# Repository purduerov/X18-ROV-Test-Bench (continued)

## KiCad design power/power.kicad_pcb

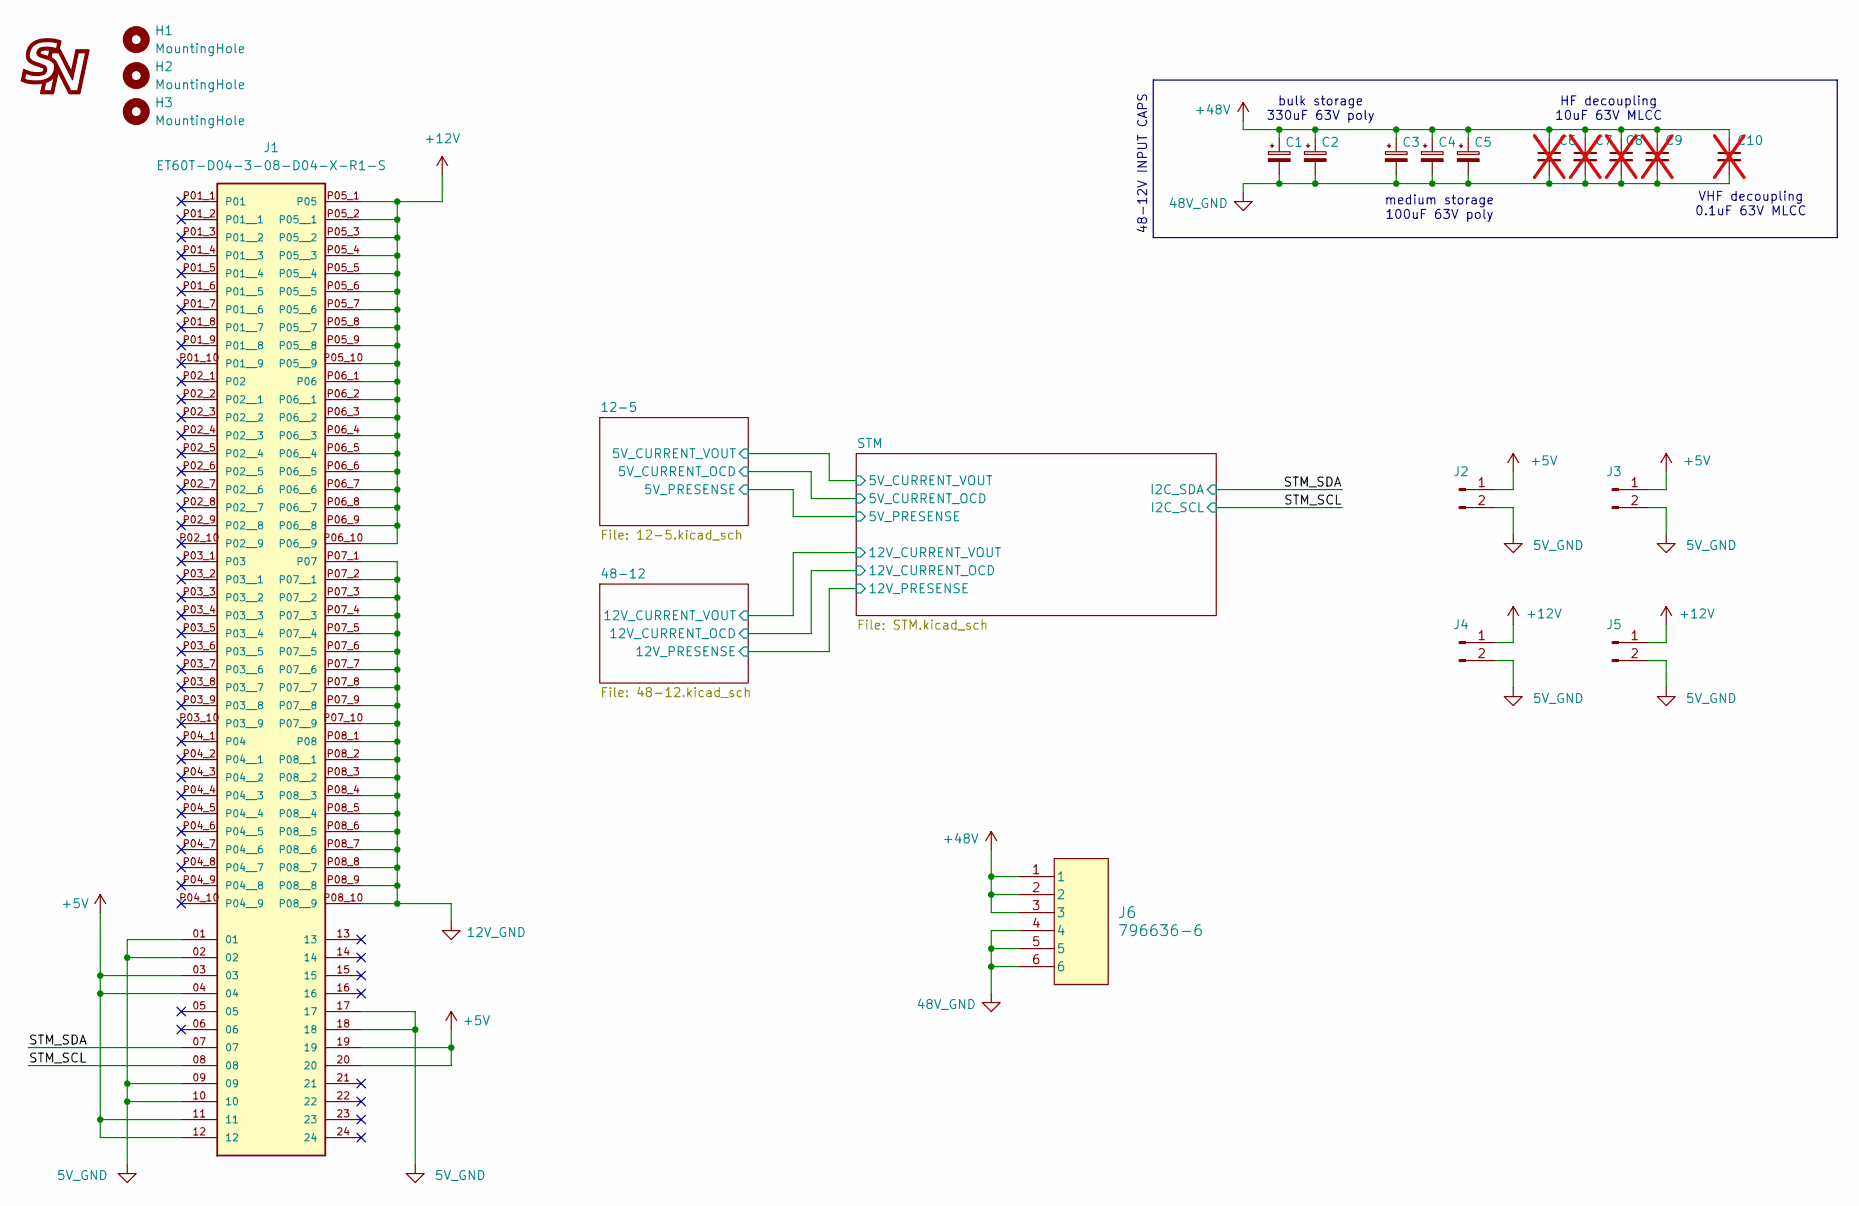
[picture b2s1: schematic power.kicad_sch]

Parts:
C1, C2: 330uF 63V poly; CP_Radial_D12.5mm_P5.00mm; MPN 63YXJ330M12.5X20; LCSC C437640
C3, C4, C5: 100uF 63V poly; CP_Radial_D8.0mm_P3.50mm; MPN RXW101M1JBK-0815; LCSC C134638
C6, C7, C8, C9: 10uF 63V; C_0603_1608Metric; not fitted
C10: 0.1uF 63V; C_0603_1608Metric; not fitted
G1: LOGO; logo
H1, H2, H3: MountingHole; MountingHole_3.2mm_M3
J1: ET60T-D04-3-08-D04-X-R1-S; SAMTEC_ET60T-D04-3-08-D04-X-R1-S
J2, J3, J4, J5: 2.54mm header; PinHeader_1x02_P2.54mm_Vertical
J6: 796636-6; MPN 796636-6

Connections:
12V_GND: J1.01, J1.02, J1.09, J1.10, J1.17, J1.18, J1.P07_1 (P07), J1.P07_2 (P07__1), J1.P07_3 (P07__2), J1.P07_4 (P07__3), J1.P07_5 (P07__4), J1.P07_6 (P07__5), J1.P07_7 (P07__6), J1.P07_8 (P07__7), J1.P07_9 (P07__8), J1.P07_10 (P07__9), J1.P08_1 (P08), J1.P08_2 (P08__1), J1.P08_3 (P08__2), J1.P08_4 (P08__3), J1.P08_5 (P08__4), J1.P08_6 (P08__5), J1.P08_7 (P08__6), J1.P08_8 (P08__7), J1.P08_9 (P08__8), J1.P08_10 (P08__9), J2.2, J3.2, J4.2, J5.2; also elsewhere on the board
48V_GND: C1.2, C2.2, C3.2, C4.2, C5.2, C6.2, C7.2, C8.2, C9.2, C10.2, J6.4, J6.5, J6.6; also elsewhere on the board
+5V: J1.03, J1.04, J1.11, J1.12, J1.19, J1.20, J2.1, J3.1; also elsewhere on the board
+12V: J1.P05_1 (P05), J1.P05_2 (P05__1), J1.P05_3 (P05__2), J1.P05_4 (P05__3), J1.P05_5 (P05__4), J1.P05_6 (P05__5), J1.P05_7 (P05__6), J1.P05_8 (P05__7), J1.P05_9 (P05__8), J1.P05_10 (P05__9), J1.P06_1 (P06), J1.P06_2 (P06__1), J1.P06_3 (P06__2), J1.P06_4 (P06__3), J1.P06_5 (P06__4), J1.P06_6 (P06__5), J1.P06_7 (P06__6), J1.P06_8 (P06__7), J1.P06_9 (P06__8), J1.P06_10 (P06__9), J4.1, J5.1; also elsewhere on the board
+48V: C1.1, C2.1, C3.1, C4.1, C5.1, C6.1, C7.1, C8.1, C9.1, C10.1, J6.1, J6.2, J6.3; also elsewhere on the board
/STM_SCL: J1.08; also elsewhere on the board
/STM_SDA: J1.07; also elsewhere on the board

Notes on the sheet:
VHF decoupling 0.1uF 63V MLCC
medium storage 100uF 63V poly
HF decoupling 10uF 63V MLCC
bulk storage 330uF 63V poly
48-12V INPUT CAPS

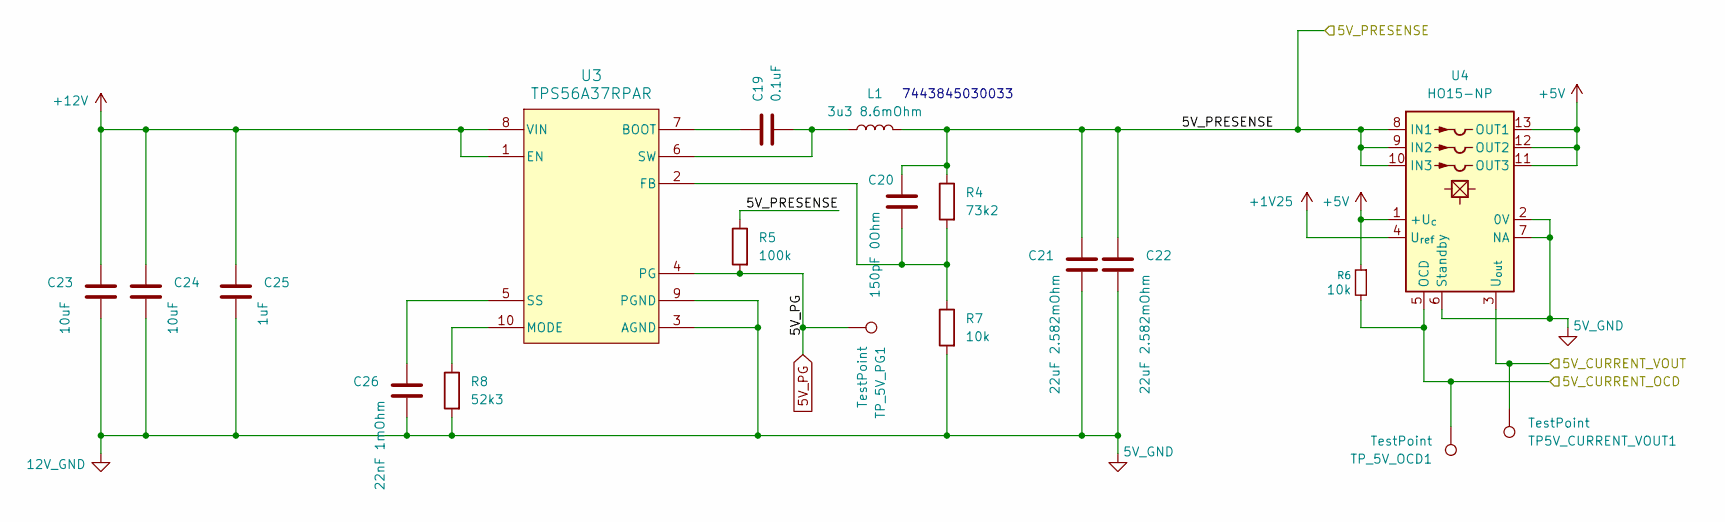
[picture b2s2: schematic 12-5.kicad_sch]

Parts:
C19: 0.1uF; C_0603_1608Metric; MPN CC0603KRX7R9BB104; LCSC C14663
C20: 150pF 0Ohm; C_0603_1608Metric; MPN CC0603JRNPO9BN151; LCSC C107038
C21, C22: 22uF 2.582mOhm; C_0603_1608Metric; MPN CL10A226MO7JZNC; LCSC C2762594
C23, C24: 10uF; C_0603_1608Metric; MPN CL10A106MA8NRNC; LCSC C96446
C25: 1uF; C_0603_1608Metric; MPN CL10A105KB8NNNC; LCSC C15849
C26: 22nF 1mOhm; C_0603_1608Metric; MPN CC0603KRX7R9BB223; LCSC C106222
L1: 3u3 8.6mOhm; WE-MXGI_5030; MPN 7443845030033
R4: 73k2; R_0603_1608Metric; MPN 0603WAF7322T5E; LCSC C14890
R5: 100k; R_0603_1608Metric; MPN 0603WAF1003T5E; LCSC C25803
R6, R7: 10k; R_0603_1608Metric; MPN 0603WAF1002T5E; LCSC C25804
R8: 52k3; R_0603_1608Metric; MPN 0603WAF5232T5E; LCSC C23198
TP5V_CURRENT_VOUT1: TestPoint; TestPoint_THTPad_2.5x2.5mm_Drill1.2mm
TP_5V_OCD1, TP_5V_PG1: TestPoint; TestPoint_THTPad_2.5x2.5mm_Drill1.2mm
U3: TPS56A37RPAR; MPN TPS56A37RPAR
U4: HO15-NP; LEM_HO8-NP; MPN HO 15-NP-0000

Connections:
5V_PG: R5.2, TP_5V_PG1.1, U3.4 (PG); also elsewhere on the board
12V_GND: C21.2, C22.2, C23.2, C24.2, C25.2, C26.2, R7.2, R8.2, U3.3 (AGND), U3.9 (PGND), U4.2 (0V), U4.6 (Standby), U4.7 (NA); also elsewhere on the board
+1V25: U4.4 (U_{ref}); also elsewhere on the board
+5V: R6.1, U4.1 (+U_{c}), U4.11 (OUT3), U4.12 (OUT2), U4.13 (OUT1); also elsewhere on the board
+12V: C23.1, C24.1, C25.1, U3.1 (EN), U3.8 (VIN); also elsewhere on the board
/12-5/5V_CURRENT_OCD: R6.2, TP_5V_OCD1.1, U4.5 (OCD); also elsewhere on the board
/12-5/5V_CURRENT_VOUT: TP5V_CURRENT_VOUT1.1, U4.3 (U_{out}); also elsewhere on the board
/12-5/5V_PRESENSE: C20.1, C21.1, C22.1, L1.2, R4.1, R5.1, U4.8 (IN1), U4.9 (IN2), U4.10 (IN3); also elsewhere on the board
unnamed: C19.1, U3.7 (BOOT)
unnamed: C20.2, R4.2, R7.1, U3.2 (FB)
unnamed: R8.1, U3.10 (MODE)
unnamed: C26.1, U3.5 (SS)
unnamed: C19.2, L1.1, U3.6 (SW)

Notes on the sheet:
7443845030033

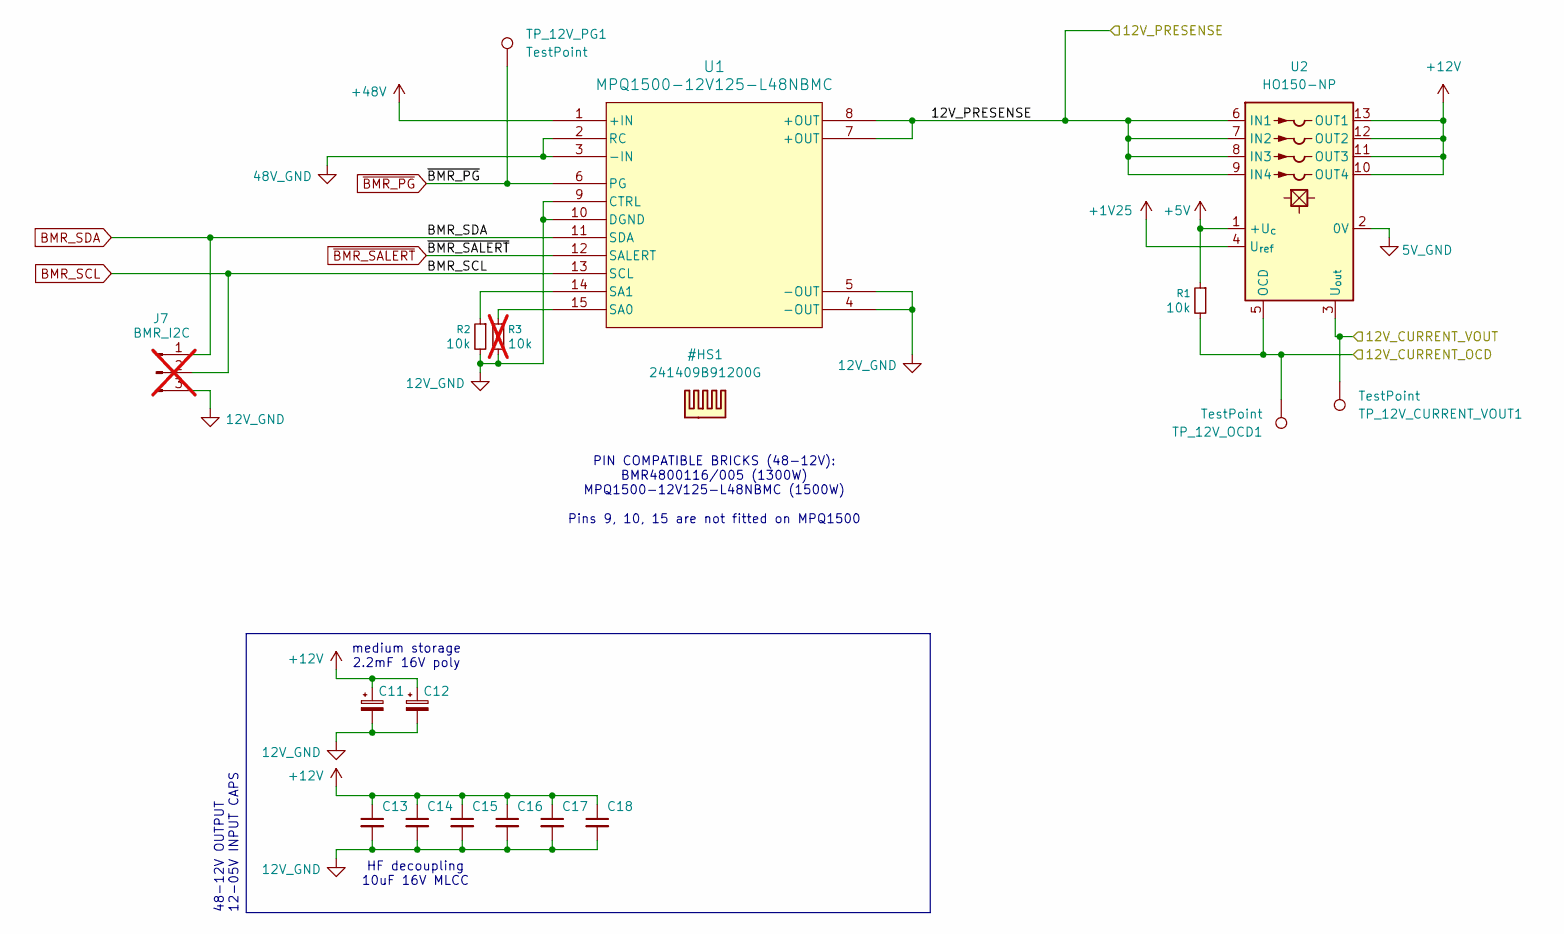
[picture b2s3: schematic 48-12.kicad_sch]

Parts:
C11, C12: 2.2mF 16V poly; CP_Radial_D18.0mm_P7.50mm; MPN GR1J222MM300A00CV0; LCSC C240374
C13, C14, C15, C16, C17, C18: 10uF; C_0603_1608Metric; MPN CL10A106MA8NRNC; LCSC C96446
J7: BMR_I2C; PinHeader_1x03_P2.54mm_Vertical; not fitted
R1, R2: 10k; R_0603_1608Metric; MPN 0603WAF1002T5E; LCSC C25804
R3: 10k; R_0603_1608Metric; MPN 0603WAF1002T5E; LCSC C25804; not fitted
TP_12V_CURRENT_VOUT1, TP_12V_OCD1, TP_12V_PG1: TestPoint; TestPoint_THTPad_2.5x2.5mm_Drill1.2mm
U1: MPQ1500-12V125-L48NBMC; BMR491_FPM; MPN MPQ1500-12V125-L48NBMC
U2: HO150-NP; LEM_HO150-NP; MPN HO 150-NP-0100

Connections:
12V_GND: C11.2, C12.2, C13.2, C14.2, C15.2, C16.2, C17.2, C18.2, J7.3, R2.2, R3.2, U1.4 (-OUT), U1.5 (-OUT), U1.9 (CTRL), U1.10 (DGND), U2.2 (0V); also elsewhere on the board
48V_GND: U1.2 (RC), U1.3 (-IN); also elsewhere on the board
+1V25: U2.4 (U_{ref}); also elsewhere on the board
+5V: R1.1, U2.1 (+U_{c}); also elsewhere on the board
+12V: C11.1, C12.1, C13.1, C14.1, C15.1, C16.1, C17.1, C18.1, U2.10 (OUT4), U2.11 (OUT3), U2.12 (OUT2), U2.13 (OUT1); also elsewhere on the board
+48V: U1.1 (+IN); also elsewhere on the board
/48-12/12V_CURRENT_OCD: R1.2, TP_12V_OCD1.1, U2.5 (OCD); also elsewhere on the board
/48-12/12V_CURRENT_VOUT: TP_12V_CURRENT_VOUT1.1, U2.3 (U_{out}); also elsewhere on the board
/48-12/12V_PRESENSE: U1.7 (+OUT), U1.8 (+OUT), U2.6 (IN1), U2.7 (IN2), U2.8 (IN3), U2.9 (IN4); also elsewhere on the board
BMR_SCL: J7.2, U1.13 (SCL); also elsewhere on the board
BMR_SDA: J7.1, U1.11 (SDA); also elsewhere on the board
unnamed: R3.1, U1.15 (SA0)
unnamed: R2.1, U1.14 (SA1)
~BMR_PG: TP_12V_PG1.1, U1.6 (PG); also elsewhere on the board
~BMR_SALERT: U1.12 (SALERT); also elsewhere on the board

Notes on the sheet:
HF decoupling 10uF 16V MLCC
PIN COMPATIBLE BRICKS (48-12V): BMR4800116/005 (1300W) MPQ1500-12V125-L48NBMC (1500W) Pins 9, 10, 15 are not fitted on MPQ1500
medium storage 2.2mF 16V poly
48-12V OUTPUT 12-05V INPUT CAPS

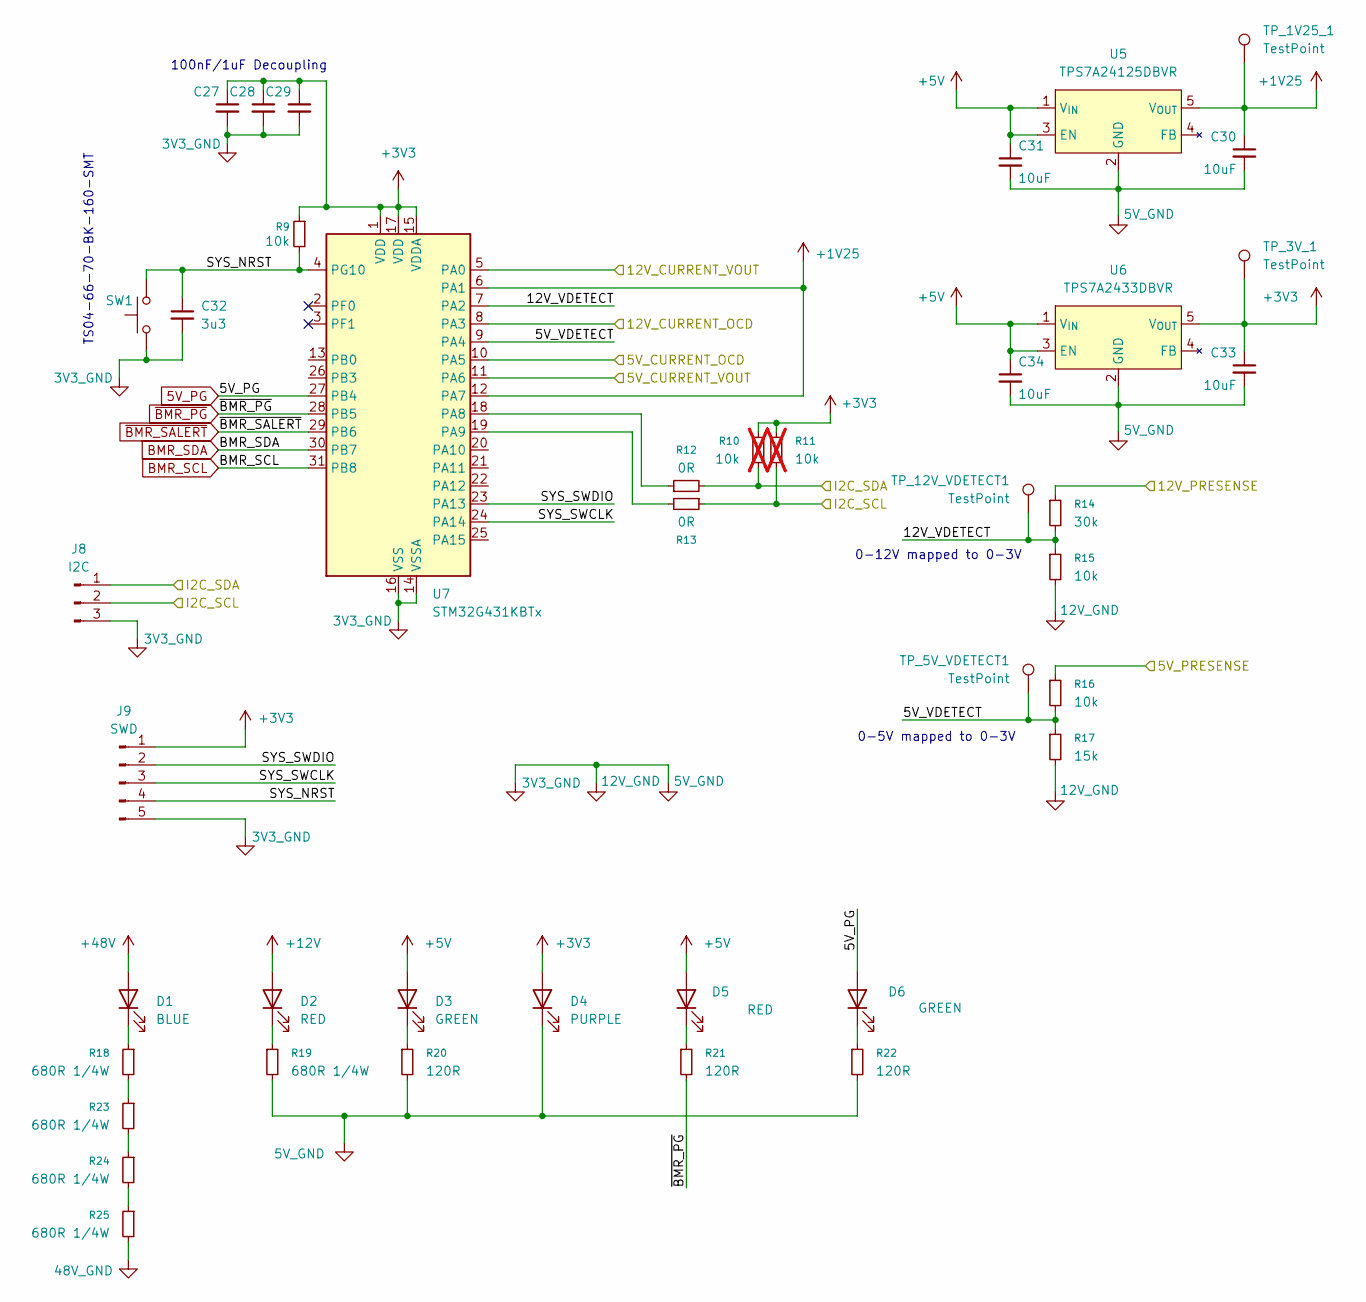
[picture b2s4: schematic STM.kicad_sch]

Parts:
C27: 0.1uF; C_0603_1608Metric; MPN CC0603KRX7R9BB104; LCSC C14663
C28, C29: 1uF; C_0603_1608Metric; MPN CL10A105KB8NNNC; LCSC C15849
C30, C31, C33, C34: 10uF; C_0603_1608Metric; MPN CL10A106MA8NRNC; LCSC C96446
C32: 3u3; C_0603_1608Metric; MPN TCC0603X5R335M250CT; LCSC C5360803
D1: BLUE; LED_0603_1608Metric; MPN XL-1608UBC-04; LCSC C965807
D2, D5: RED; LED_0603_1608Metric; MPN XL-1608SURC-06; LCSC C965799
D3, D6: GREEN; LED_0603_1608Metric; MPN XL-1608UGC-04; LCSC C965804
D4: PURPLE; LED_0603_1608Metric; MPN XL-1608UVC-04; LCSC C7371898
J8: I2C; PinHeader_1x03_P2.54mm_Vertical
J9: SWD; PinHeader_1x05_P2.54mm_Vertical
R9, R15, R16: 10k; R_0603_1608Metric; MPN 0603WAF1002T5E; LCSC C25804
R10, R11: 10k; R_0603_1608Metric; MPN 0603WAF1002T5E; LCSC C25804; not fitted
R12, R13: 0R; R_0603_1608Metric; MPN 0603WAF0000T5E; LCSC C21189
R14: 30k; R_0603_1608Metric; MPN 0603WAF3002T5E; LCSC C22984
R17: 15k; R_0603_1608Metric; MPN 0603WAF1502T5E; LCSC C22809
R18, R19, R23, R24, R25: 680R 1/4W; R_0603_1608Metric; MPN ERJPA3J681V; LCSC C445820
R20, R21, R22: 120R; R_0603_1608Metric; MPN 0603WAF1200T5E; LCSC C22787
SW1: SW_Push; TS04-66-70-BK-160-SMT; MPN TS04-66-70-BK-160-SMT; LCSC C455109
TP_1V25_1, TP_3V_1, TP_5V_VDETECT1, TP_12V_VDETECT1: TestPoint; TestPoint_THTPad_2.5x2.5mm_Drill1.2mm
U5: TPS7A24125DBVR; SOT-23-5; MPN TPS7A24125DBVR
U6: TPS7A2433DBVR; SOT-23-5; MPN TPS7A2433DBVR
U7: STM32G431KBTx; LQFP-32_7x7mm_P0.8mm; MPN STM32G431KBT6

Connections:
5V_PG: D6.2 (A), U7.27 (PB4); also elsewhere on the board
12V_GND: C27.2, C28.2, C29.2, C30.2, C31.2, C32.2, C33.2, C34.2, D4.1 (K), J8.3, J9.5, R15.2, R17.2, R19.2, R20.2, R22.2, SW1.1, U5.2 (GND), U6.2 (GND), U7.14 (VSSA), U7.16 (VSS), U7.32 (VSS); also elsewhere on the board
48V_GND: R25.2; also elsewhere on the board
+1V25: C30.1, TP_1V25_1.1, U5.5 (V_{OUT}), U7.6 (PA1), U7.12 (PA7); also elsewhere on the board
+3V3: C27.1, C28.1, C29.1, C33.1, D4.2 (A), J9.1, R9.1, R10.1, R11.1, TP_3V_1.1, U6.5 (V_{OUT}), U7.1 (VDD), U7.15 (VDDA), U7.17 (VDD)
+5V: C31.1, C34.1, D3.2 (A), D5.2 (A), U5.1 (V_{IN}), U5.3 (EN), U6.1 (V_{IN}), U6.3 (EN); also elsewhere on the board
+12V: D2.2 (A); also elsewhere on the board
+48V: D1.2 (A); also elsewhere on the board
/12-5/5V_CURRENT_OCD: U7.10 (PA5); also elsewhere on the board
/12-5/5V_CURRENT_VOUT: U7.11 (PA6); also elsewhere on the board
/12-5/5V_PRESENSE: R16.1; also elsewhere on the board
/48-12/12V_CURRENT_OCD: U7.8 (PA3); also elsewhere on the board
/48-12/12V_CURRENT_VOUT: U7.5 (PA0); also elsewhere on the board
/48-12/12V_PRESENSE: R14.1; also elsewhere on the board
/STM/5V_VDETECT: R16.2, R17.1, TP_5V_VDETECT1.1, U7.9 (PA4)
/STM/12V_VDETECT: R14.2, R15.1, TP_12V_VDETECT1.1, U7.7 (PA2)
/STM/SYS_NRST: C32.1, J9.4, R9.2, SW1.2, U7.4 (PG10)
/STM/SYS_SWCLK: J9.3, U7.24 (PA14)
/STM/SYS_SWDIO: J9.2, U7.23 (PA13)
/STM_SCL: J8.2, R11.2, R13.1; also elsewhere on the board
/STM_SDA: J8.1, R10.2, R12.2; also elsewhere on the board
BMR_SCL: U7.31 (PB8); also elsewhere on the board
BMR_SDA: U7.30 (PB7); also elsewhere on the board
unnamed: D1.1 (K), R18.1
unnamed: D2.1 (K), R19.1
unnamed: D3.1 (K), R20.1
unnamed: D5.1 (K), R21.1
unnamed: D6.1 (K), R22.1
unnamed: R18.2, R23.1
unnamed: R23.2, R24.1
unnamed: R24.2, R25.1
unnamed: R12.1, U7.18 (PA8)
unnamed: R13.2, U7.19 (PA9)
~BMR_PG: R21.2, U7.28 (PB5); also elsewhere on the board
~BMR_SALERT: U7.29 (PB6); also elsewhere on the board

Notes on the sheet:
100nF/1uF Decoupling
0-5V mapped to 0-3V
TS04-66-70-BK-160-SMT
0-12V mapped to 0-3V

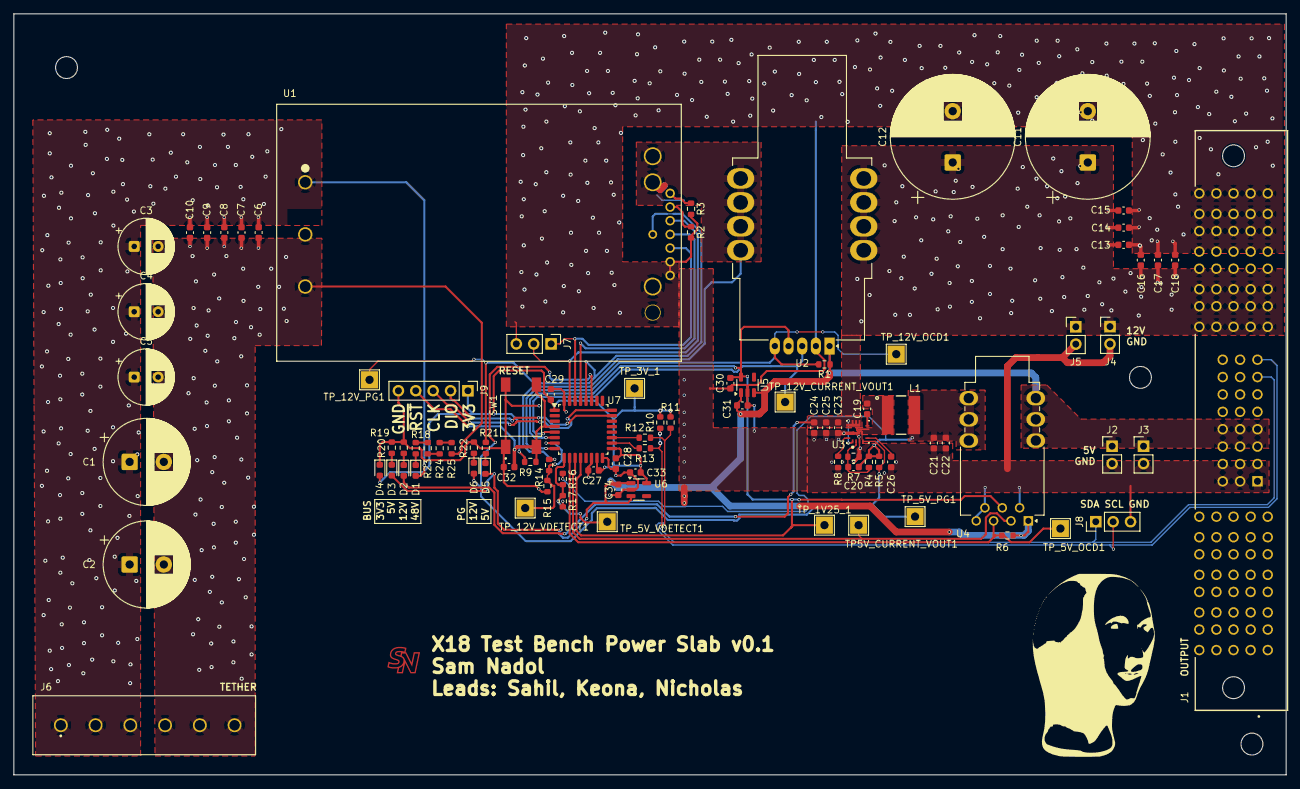
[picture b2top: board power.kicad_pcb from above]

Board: 2 copper layers, 186.0 x 111.2 mm, 97 parts (0 on the bottom side), 42 nets.

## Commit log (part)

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2025-09-20 start of board, footprints etc
2025-09-27 work
2025-10-04 stuff
2025-10-14 initial
2025-10-14 added some testpoints and some labeling
2025-10-18 added leds and minor fixes
2025-10-23 minor edits
2025-10-25 pretty much done i think
2025-11-06 pretty much done
2025-11-17 final
2025-11-30 started routing
2025-12-06 yeet
2025-12-06 push before autoroute test, everything done except pi breakout
2025-12-06 split pi connector
2025-12-06 basically done, added a bunch of vias for no reason, for love of the game
2025-12-28 basically done
2025-12-28 added names and pete
2026-01-05 added vias and some silkscreen art
2026-01-14 type shi
2026-01-15 bom updated stuff
2026-01-15 commit ig
